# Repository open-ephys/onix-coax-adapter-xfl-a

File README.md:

# ONIX X.Coax Adapter Boards
Coaxial micro-tether interface for the following headstages and miniscopes

| Revision | Compatibility | Status |
|-|-|-|
| X.FL\rev1.0 | Headstage-64 | Produced and validated |
| X.FL\rev1.1 | Headstage-64 | Not produced |
| X.FL\rev1.2 | Headstage-64 | Produced and validated |
| X.FL\rev2.0 | Headstage-64s <br /> Headstage-16Stim <br /> Headstage-RHS2116 <br /> Kiloscope | Produced and validated |
| U.FL\rev1.0 | Headstage-64 | Not produced |

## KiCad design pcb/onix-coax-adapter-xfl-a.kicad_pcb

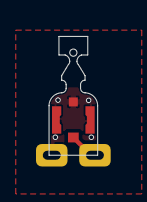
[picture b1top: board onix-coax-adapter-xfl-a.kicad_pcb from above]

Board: 2 copper layers, 2.7 x 6.6 mm, 3 parts (0 on the bottom side), 2 nets.

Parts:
J1: Conn_Coaxial; LINX_CONMHF4-SMD-G
TP1, TP2: TestPoint; Castellation

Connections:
/GND: J1.2 (Ext), TP2.1
/SIG: J1.1 (In), TP1.1

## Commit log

2022-12-29 Moved current design to X.FL\rev2.0
    The current designed is considered to be revision 2.0.
2022-12-29 Added the very first version (rev1.0).
    This version was designed by @jonnew to interface with the first version of the ONIX Headstage-64
2022-12-29 Added rev1.1.
    This version was not used.
2022-12-29 Added rev1.2.
2022-12-29 Added the first attempt of using an U.FL connector.
2022-12-29 Added compatibility table.
